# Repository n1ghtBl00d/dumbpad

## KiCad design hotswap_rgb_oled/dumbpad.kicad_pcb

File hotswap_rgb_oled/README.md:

# dumbpad - Hotswap - RGB - OLED

Designed by [n1ghtBl00d](https://www.github.com/n1ghtBl00d).

## Description

Combination of the Hotswap and OLED variants

### Revisions

- 3.1 Initial published PCB
- 3.2 Replaced Indicator LEDs with OLED Screen socket

#### dumbpad v3.1

#### Renders

### Bill of materials

* 16x Kailh Hotswap Sockets (rev 2)
* 16x Cherry-style mechanical switches
* 17x 1n4148 diodes (thru hole)
* 1x Arduino Pro Micro or pin-compatible ATmega32u4-based MCU
* 1x EC11 rotary encoder with pushbutton (7-pin)
* (optional) 16x SK6812 mini e LEDs
* (optional) 1x 6mm tactile switch (to reset MCU)
* (optional) 3x 3mm LEDs (whatever color)
* (optional) 3x 330ohm or similar resistors for the LEDS (not needed if not adding LEDs)

## Making the PCB

Submit either the KiCad `.kicad_pcb` or the gerber files to your prefered PCB manufacturer.

### Notes on soldering

It's recommended to start with the Sockets and then add the remaining parts.

Solder the SK6812 LEDs with the missing corners aligned with the corners printed on the PCB as shown in the image.

*NOTE:* the orientation of the LEDs changes between the lines!

## Acknowledgements

Some of the footprints are extracted from the awesome [Corne Keyboard](https://github.com/foostan/crkbd) by [Kosuke Adachi](https://github.com/foostan).

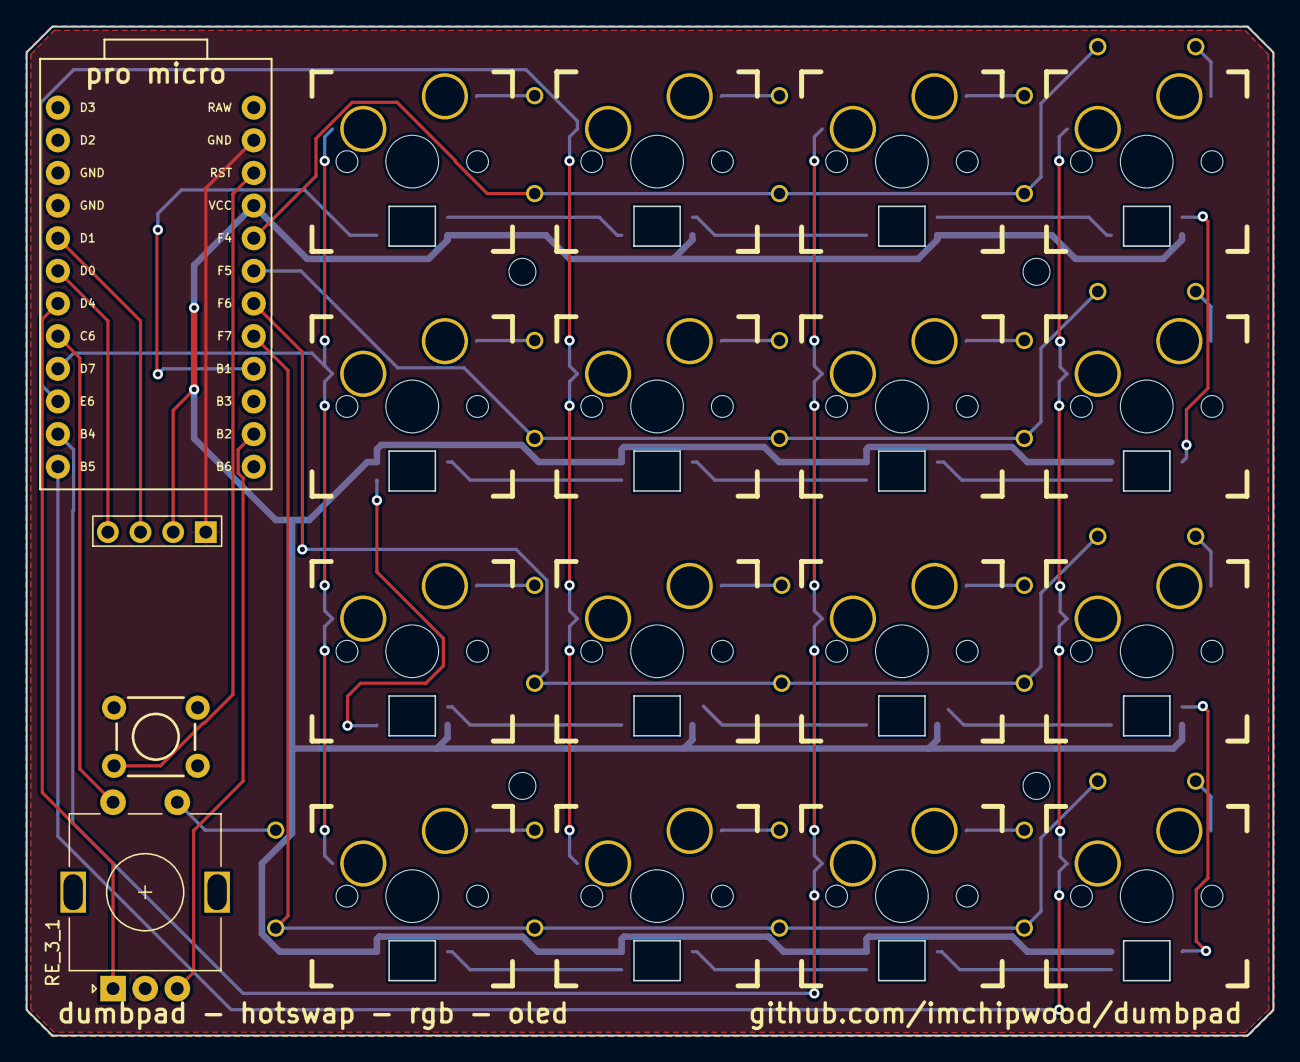
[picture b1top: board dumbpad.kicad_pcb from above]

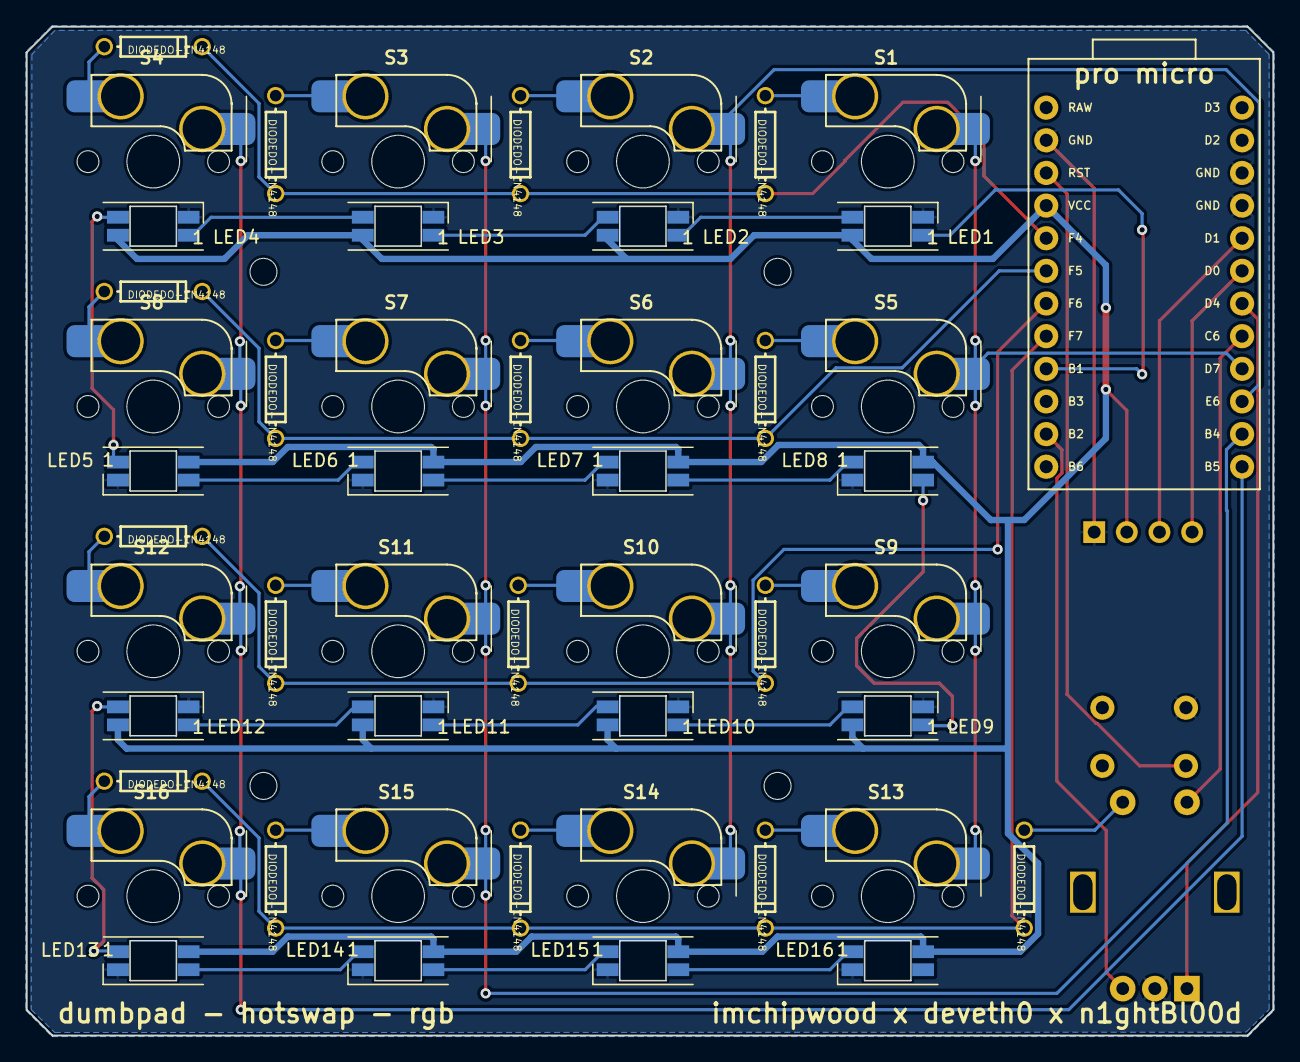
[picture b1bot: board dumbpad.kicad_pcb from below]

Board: 2 copper layers, 97.0 x 78.5 mm, 53 parts (49 on the bottom side), 49 nets.

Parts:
B1: SPARKFUN_PRO_MICRO
D1, D2, D3, D4, D5, D6, D7, D8, D9, D10, D11, D12, D13, D14, D15, D16, D20: DIODEDO-1N4148; DO-1N4148
J1: Conn_01x04_Female; OLED
LED1, LED2, LED3, LED4, LED5, LED6, LED7, LED8, LED9, LED10, LED11, LED12, LED13, LED14, LED15, LED16: SK6812MINI; YS-SK6812MINI-E
RE_3_1: CHERRY-MX-ENCODER; RotaryEncoder_Alps_EC11E-Switch_Vertical_H20mm
S1, S2, S3, S4, S5, S6, S7, S8, S9, S10, S11, S12, S13, S14, S15, S16: MOMENTARY-SWITCH-SPST-LED-PTH-CHERRY; Kailh-CPG151101S11_MX_Socket-1.00u
S17: MOMENTARY-SWITCH-SPST-PTH-6.0MM; TACTILE_SWITCH_PTH_6.0MM

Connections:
/COL0: B1.8 (*5), RE_3_1.S2 (2)
/COL1: B1.9 (*6), S1.S2 (2), S5.S2 (2), S9.S2 (2), S13.S2 (2)
/COL2: B1.10 (7), S2.S2 (2), S6.S2 (2), S10.S2 (2), S14.S2 (2)
/COL3: B1.11 (8), S3.S2 (2), S7.S2 (2), S11.S2 (2), S15.S2 (2)
/COL4: B1.12 (*9), S4.S2 (2), S8.S2 (2), S12.S2 (2), S16.S2 (2)
/ENCODER0_L0: B1.14 (11(MOSI)), RE_3_1.B
/ENCODER0_L1: B1.7 (4), RE_3_1.A
/KEY_LEDS: B1.16 (13(SCK)), LED1.4 (DIN)
/RESET: B1.22 (RESET), S17.3 (2)
/ROW0: B1.20 (A3), D1.C, D2.C, D3.C, D4.C
/ROW1: B1.19 (A2), D5.C, D6.C, D7.C, D8.C
/ROW2: B1.18 (A1), D9.C, D10.C, D11.C, D12.C
/ROW3: B1.17 (A0), D13.C, D14.C, D15.C, D16.C, D20.C
/SCL: B1.5 (2), J1.3
/SDA: B1.6 (*3), J1.4
GND: B1.3 (GND@1), B1.4 (GND), B1.23 (GND@2), J1.1, LED1.3 (VSS), LED2.3 (VSS), LED3.3 (VSS), LED4.3 (VSS), LED5.3 (VSS), LED6.3 (VSS), LED7.3 (VSS), LED8.3 (VSS), LED9.3 (VSS), LED10.3 (VSS), LED11.3 (VSS), LED12.3 (VSS), LED13.3 (VSS), LED14.3 (VSS), LED15.3 (VSS), LED16.3 (VSS), RE_3_1.C, S17.1
unnamed: D1.A, S1.S1 (1)
unnamed: D2.A, S2.S1 (1)
unnamed: D3.A, S3.S1 (1)
unnamed: D4.A, S4.S1 (1)
unnamed: D5.A, S5.S1 (1)
unnamed: D6.A, S6.S1 (1)
unnamed: D7.A, S7.S1 (1)
unnamed: D8.A, S8.S1 (1)
unnamed: D9.A, S9.S1 (1)
unnamed: D10.A, S10.S1 (1)
unnamed: D11.A, S11.S1 (1)
unnamed: D12.A, S12.S1 (1)
unnamed: D13.A, S13.S1 (1)
unnamed: D14.A, S14.S1 (1)
unnamed: D15.A, S15.S1 (1)
unnamed: D16.A, S16.S1 (1)
unnamed: D20.A, RE_3_1.S1 (1)
unnamed: LED1.2 (DOUT), LED2.4 (DIN)
unnamed: LED2.2 (DOUT), LED3.4 (DIN)
unnamed: LED3.2 (DOUT), LED4.4 (DIN)
unnamed: LED4.2 (DOUT), LED5.4 (DIN)
unnamed: LED5.2 (DOUT), LED6.4 (DIN)
unnamed: LED6.2 (DOUT), LED7.4 (DIN)
unnamed: LED7.2 (DOUT), LED8.4 (DIN)
unnamed: LED8.2 (DOUT), LED9.4 (DIN)
unnamed: LED10.2 (DOUT), LED11.4 (DIN)
unnamed: LED9.2 (DOUT), LED10.4 (DIN)
unnamed: LED11.2 (DOUT), LED12.4 (DIN)
unnamed: LED12.2 (DOUT), LED13.4 (DIN)
unnamed: LED13.2 (DOUT), LED14.4 (DIN)
unnamed: LED14.2 (DOUT), LED15.4 (DIN)
unnamed: LED15.2 (DOUT), LED16.4 (DIN)
VCC: B1.21 (VCC), J1.2, LED1.1 (VDD), LED2.1 (VDD), LED3.1 (VDD), LED4.1 (VDD), LED5.1 (VDD), LED6.1 (VDD), LED7.1 (VDD), LED8.1 (VDD), LED9.1 (VDD), LED10.1 (VDD), LED11.1 (VDD), LED12.1 (VDD), LED13.1 (VDD), LED14.1 (VDD), LED15.1 (VDD), LED16.1 (VDD)

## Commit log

2022-11-12 Added Hotswap/OLED variant
2022-11-12 Updated silkscreen text
2022-11-12 Updated back silkscreen text
2022-11-12 Renamed gerber output folder and updated zip file
